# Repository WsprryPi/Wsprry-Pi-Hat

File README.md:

# Wsprry Pi KiCad Files

Within this repository are the KiCad files supporting Wsprry Pi.  UNless otherwise noted, these should be considered untested and not ready for production.

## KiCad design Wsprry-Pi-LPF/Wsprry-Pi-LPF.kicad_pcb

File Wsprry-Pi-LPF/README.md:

# Wsprry Pi LPF Board

This design is for the LPF board.

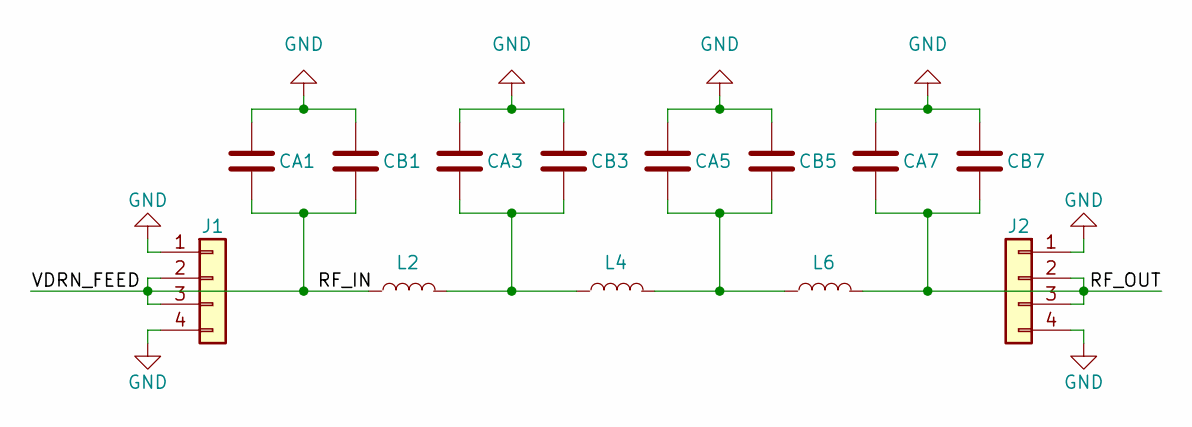
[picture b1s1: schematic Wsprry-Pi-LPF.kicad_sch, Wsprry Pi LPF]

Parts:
CA1, CA3, CA5, CA7: C; C_Disc_D3.0mm_W1.6mm_P2.50mm
CB1, CB3, CB5, CB7: C; C_Disc_D3.0mm_W1.6mm_P2.50mm
J1, J2: Conn_01x04; PinHeader_1x04_P2.54mm_Vertical; LCSC_PART C2718488
L2, L4, L6: L; L_Axial_Horiz_Torroid_Vert_12mm_D5mm_P10.2mm

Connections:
/RF_IN: CA1.2, CB1.2, J1.2, J1.3, L2.1
/RF_OUT: CA7.2, CB7.2, J2.2, J2.3, L6.2
GND: CA1.1, CA3.1, CA5.1, CA7.1, CB1.1, CB3.1, CB5.1, CB7.1, J1.1, J1.4, J2.1, J2.4
unnamed: CA3.2, CB3.2, L2.2, L4.1
unnamed: CA5.2, CB5.2, L4.2, L6.1

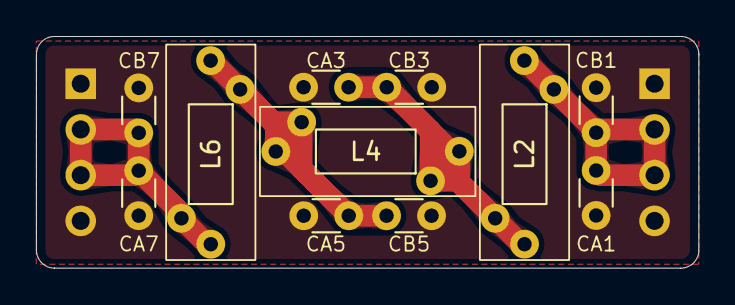
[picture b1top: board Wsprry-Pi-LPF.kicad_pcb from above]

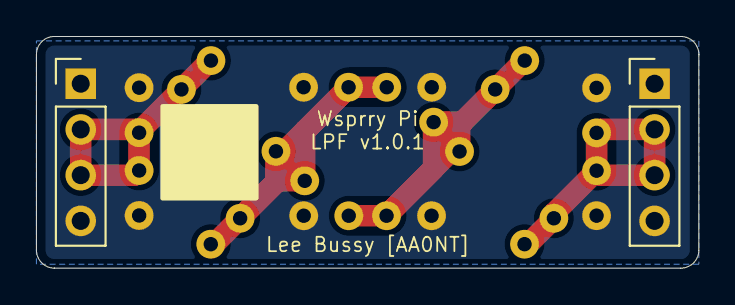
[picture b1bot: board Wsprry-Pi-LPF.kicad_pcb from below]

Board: 2 copper layers, 36.8 x 12.9 mm, 13 parts (2 on the bottom side), 5 nets.

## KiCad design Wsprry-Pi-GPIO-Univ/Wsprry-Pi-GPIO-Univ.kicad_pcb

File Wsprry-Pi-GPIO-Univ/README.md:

# Wsprry Pi GPIO Board

This design is for the traditional GPIO transmission board.

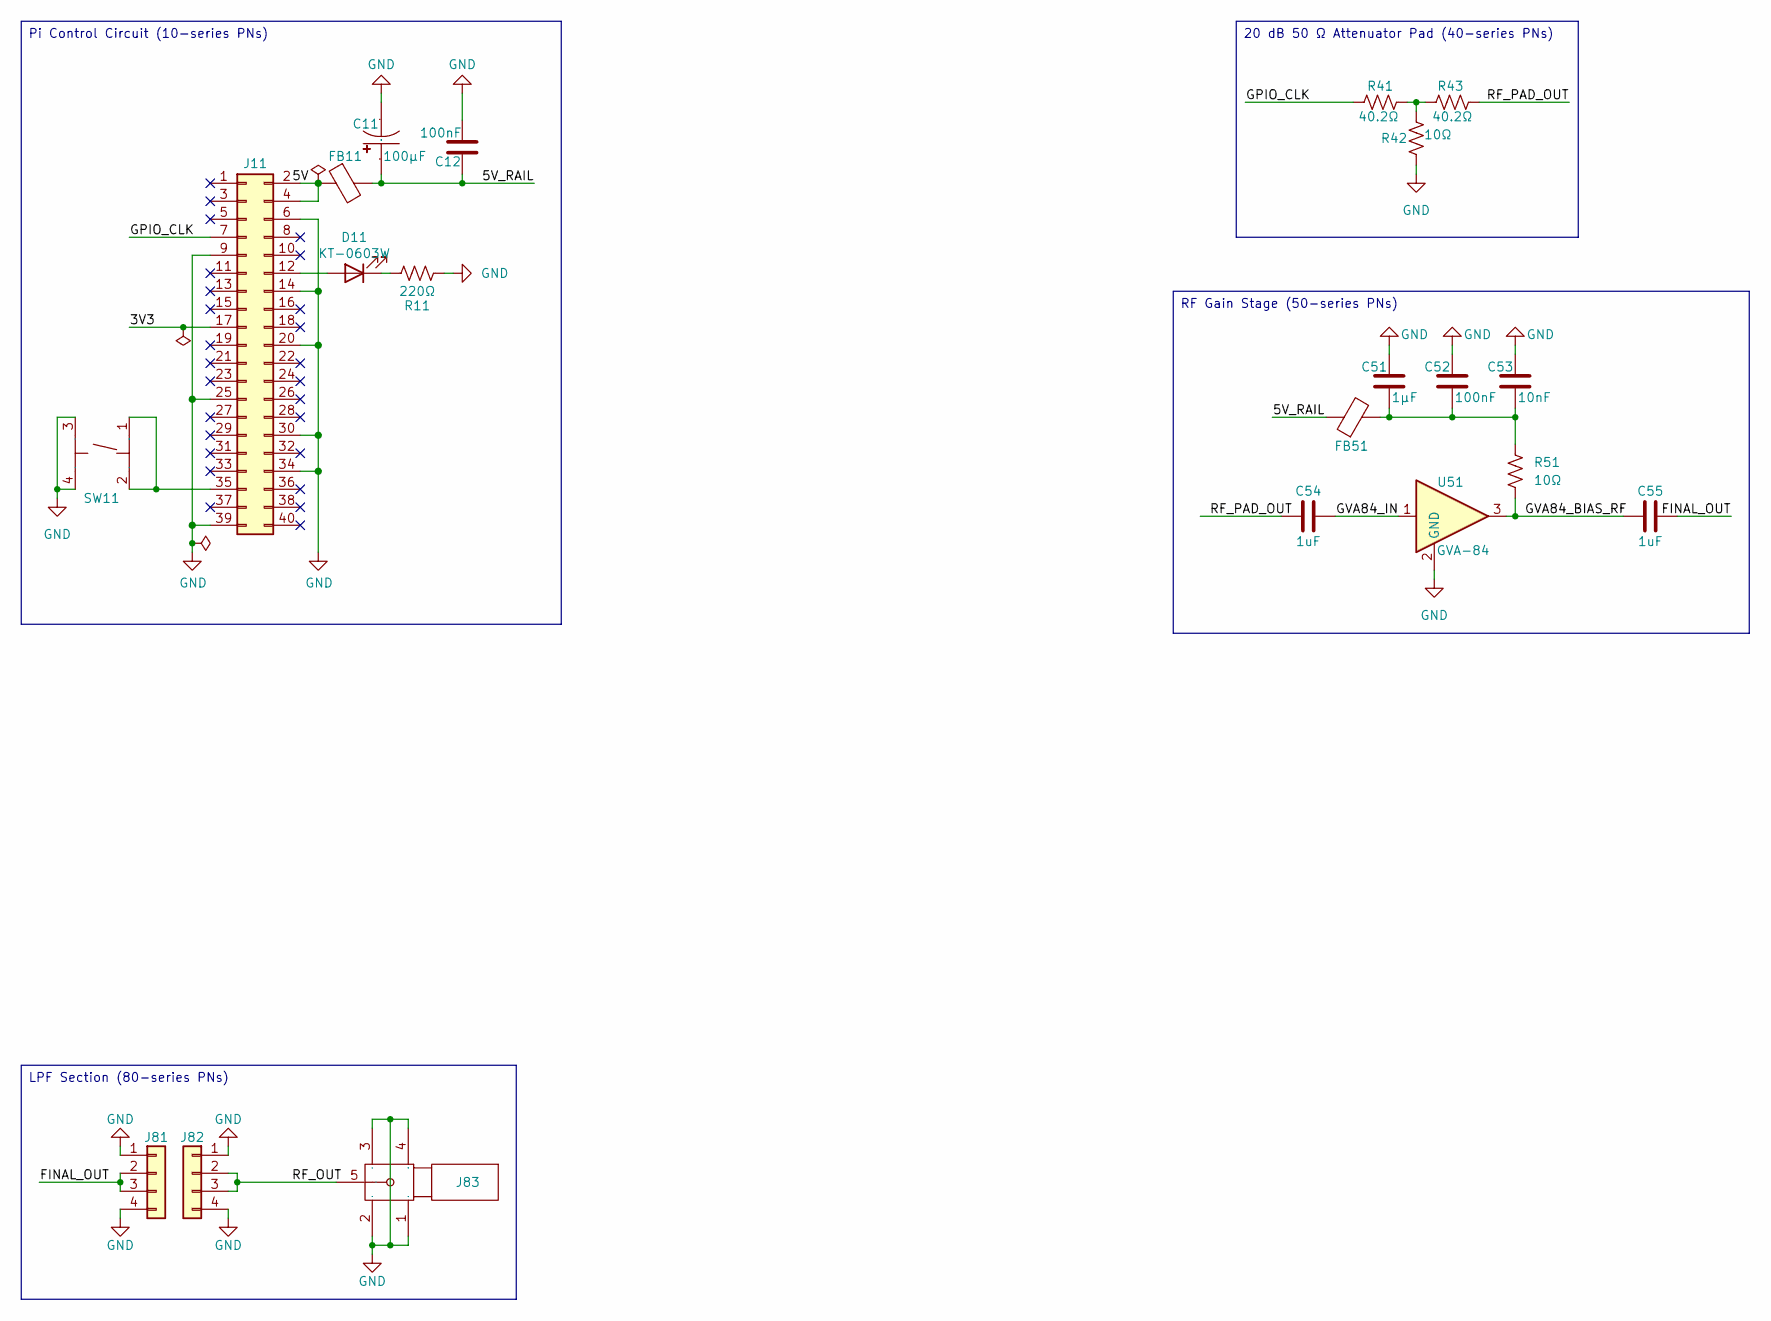
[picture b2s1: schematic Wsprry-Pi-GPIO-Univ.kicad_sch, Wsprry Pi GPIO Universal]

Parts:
C11: 100µF; CAP-SMD_BD6.3-L6.6-W6.6-FD; LCSC_PART C178565
C12: 100nF; C_0603_1608Metric; LCSC_PART C14663
C51: 1µF; C_0603_1608Metric; LCSC_PART C15849
C52: 100nF; C_0402_1005Metric; LCSC_PART C307331
C53: 10nF; C_0402_1005Metric; LCSC_PART C15195
C54, C55: 1uF; C_0805_2012Metric; LCSC_PART C28323
D11: KT-0603W; LED_0603_1608Metric; LCSC_PART C2286
FB11, FB51: 600Ω@100MHz; L_0603_1608Metric; LCSC_PART C107335
J11: GPIO; PinSocket_2x20_P2.54mm_Vertical; LCSC_PART C2977589
J81, J82: Conn_01x04; PinSocket_1x04_P2.54mm_Vertical; LCSC_PART C2718488
J83: SMA; SMA-TH_BWSMA-KWE-Z001; Manufacturer Part BWSMA-KWE-Z001; LCSC_PART C496551
R11: 220Ω; R_0603_1608Metric; LCSC_PART C22962
R41, R43: 40.2Ω; R_0603_1608Metric; LCSC_PART C705775
R42: 10Ω; R_0603_1608Metric; LCSC_PART C217691
R51: 10Ω; R_0805_2012Metric; LCSC_PART C17415
SW11: Switch; SW-SMD_4P-L5.1-W5.1-P3.70-LS6.5-TL_H1.5; LCSC_PART C318884
U51: GVA-84; SOT-89-3; LCSC_PART C5445191

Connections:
/3V3: J11.17
/5V: FB11.1, J11.2, J11.4
/5V_RAIL: C11.1, C12.1, FB11.2, FB51.1
/FINAL_OUT: C55.2, J81.2, J81.3
/GPIO_CLK: J11.7, R41.1
/GVA84_BIAS_RF: C55.1, R51.2, U51.3
/GVA84_IN: C54.2, U51.1
/RF_OUT: J82.2, J82.3, J83.5
/RF_PAD_OUT: C54.1, R43.2
GND: C11.2, C12.2, C51.2, C52.2, C53.2, J11.6, J11.9, J11.14, J11.20, J11.25, J11.30, J11.34, J11.39, J81.1, J81.4, J82.1, J82.4, J83.1, J83.2, J83.3, J83.4, R11.1, R42.1, SW11.3 (C), SW11.4 (D), U51.2 (GND)
unnamed: C51.1, C52.1, C53.1, FB51.2, R51.1
unnamed: D11.2 (A), J11.12
unnamed: D11.1 (K), R11.2
unnamed: J11.35, SW11.1 (A), SW11.2 (B)
unnamed: R41.2, R42.2, R43.1

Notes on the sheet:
20 dB 50 Ω Attenuator Pad (40-series PNs)
Pi Control Circuit (10-series PNs)
RF Gain Stage (50-series PNs)
LPF Section (80-series PNs)

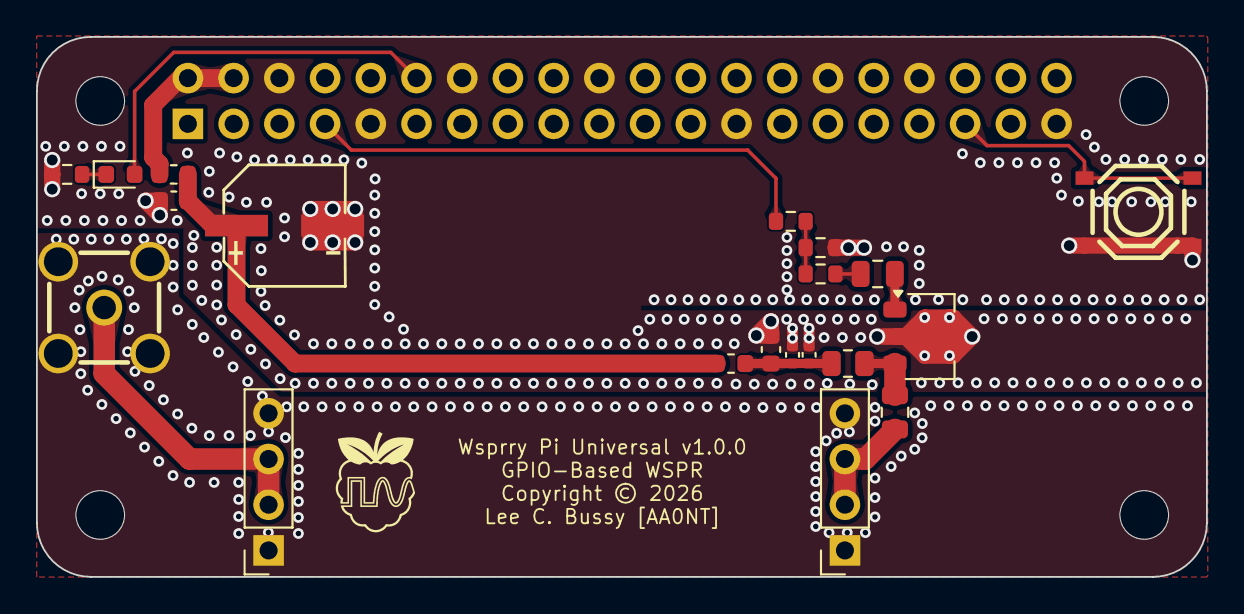
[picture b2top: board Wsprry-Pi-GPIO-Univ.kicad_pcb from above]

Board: 2 copper layers, 65.0 x 30.0 mm, 25 parts (1 on the bottom side), 14 nets.

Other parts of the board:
MH1, MH2, MH3, MH4: MountingHole_2.7mm_M2.5

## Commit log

2026-04-30 Enlarge axial L pad, add Toroid co-pad

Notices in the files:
Wsprry-Pi-GPIO-Univ/Wsprry-Pi-GPIO-Univ.kicad_pcb:
Copyright © 2026
